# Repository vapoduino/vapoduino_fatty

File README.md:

# Vapoduino Fatty

**NOTE:** This is a prototype which was made as a proof-of-concept. It is funcitonal, but there will not be any further development

This is an eralier prototype of the open source herbs vaporizer from [acidg/vape_model](https://github.com/acidg/vape_model).
It features a Bluetooth connection and an app, which can be found under [acidg/vape_app](https://github.com/acidg/vape_app).

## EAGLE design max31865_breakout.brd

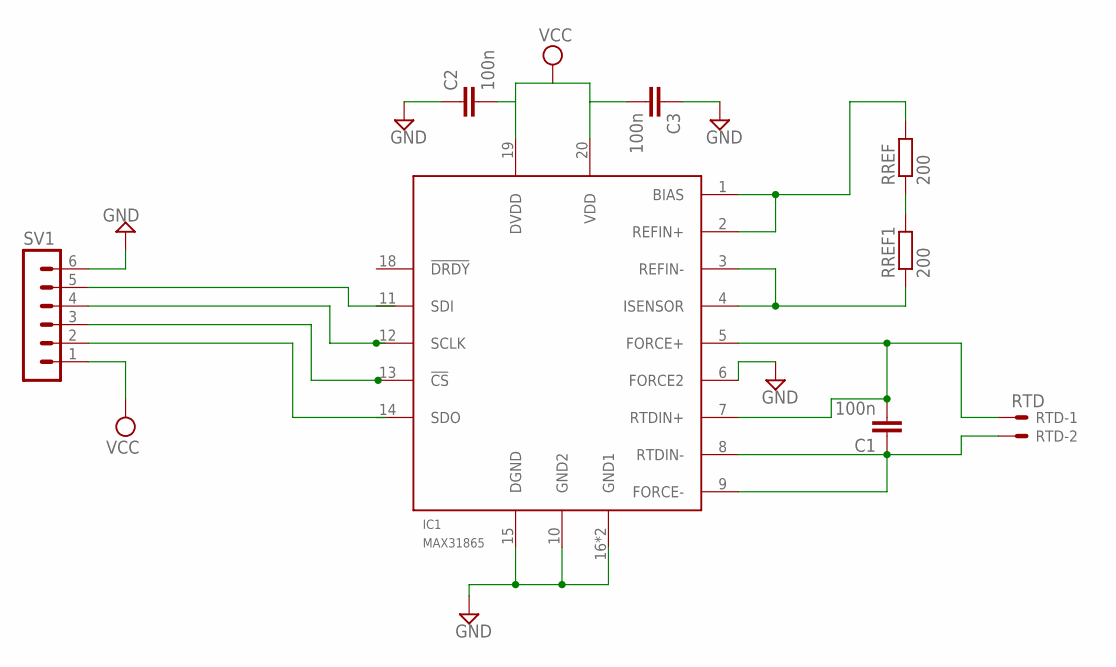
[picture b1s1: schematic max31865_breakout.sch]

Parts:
C1, C2, C3: 100n; C0805K
IC1: MAX31865; TQFN20-5X5
RREF, RREF1: 200; M1206
RTD: RTD; 22-23-2021
SV1: MA06-1

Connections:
CS: SV1.3
GND: C2.1, C3.1, IC1.6 (FORCE2), IC1.10 (GND2), IC1.15 (DGND), IC1.16 (GND1), IC1.EXP (GND1), SV1.6
unnamed: RREF.1, RREF1.2
REFIN+: IC1.1 (BIAS), IC1.2 (REFIN+), RREF.2
REFIN-: IC1.3 (REFIN-), IC1.4 (ISENSOR), RREF1.1
RTD+: C1.2, IC1.5 (FORCE+), IC1.7 (RTDIN+), RTD.1
RTD-: C1.1, IC1.8 (RTDIN-), IC1.9 (FORCE-), RTD.2
SCLK: IC1.12 (SCLK), SV1.4
SDI: SV1.5
SDO: SV1.2
VCC: C2.2, C3.2, IC1.19 (DVDD), IC1.20 (VDD), SV1.1

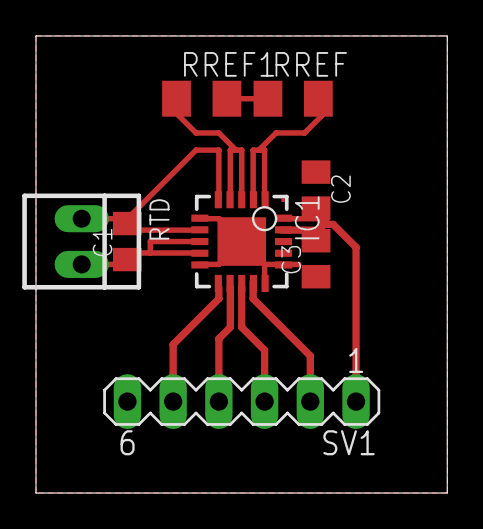
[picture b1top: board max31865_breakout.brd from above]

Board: 2 copper layers, 22.8 x 25.4 mm, 8 parts (0 on the bottom side), 8 nets.

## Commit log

2016-07-17 Import old code, add bluetoooth serial
2016-07-17 adding select temp via bluetooth feature
2016-07-17 shuting down heat, when command is received
2016-07-18 removing standby, adding battery percents to output
2016-07-18 addign pid change via serial commands
2016-10-02 adding plattformio stuff
2017-07-09 Using slowber ide
2017-07-19 enabling change of pid with bt app
2017-07-20 removing sloeber stuff
2017-07-20 removing serialPlotter.py
2018-02-24 adding picture, updating readme
2018-05-09 Adding schematics and PCB for MAX31865 breakout board
2018-05-09 Adding more pictures
2018-05-09 Adding instrution pictures
2018-05-18 adding fritzing schematic
2018-05-18 adding annotated schematic
2018-05-19 adding image of electronics bay
2018-05-19 adding image of coil winding
